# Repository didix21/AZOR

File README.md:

# AZOR

This repository contains all the AZOR 1.0 board KiCad files.  

## About Hardware 

AZOR 1.0 is based on [DUET 0.85](http://reprap.org/wiki/Duet#Drive_numbers) created by [dc42](https://github.com/dc42). I have done very important modifications as delete Ethernet and micro SD ports. Instead, I have added a USB 2.0 port to read USB Sticks. 

Moreover, the integrated steppers A4982 have been deleted and instead of that, I have placed HEADER PINS to connect drivers as A4988 or DRV8825. 

## About Software 

AZOR 1.0 use [Marlin4AZOR](https://github.com/didix21/Marlin4AZOR), it is a modified version of work  done by [Wurstnase](https://github.com/Wurstnase). In other words it is based on [Marlin4Due](https://github.com/Wurstnase/Marlin4Due).

## Main Features

- MCU: 32-bits, ATSAM3X8E-AU.
- Port Expansion
- Support for drivers: A4982 and DRV8825.
- Two FAN PWM ports.
- PTS-Panel Header Pin port.
- SD Header Pin Port.
- USB 2.0 port.

## License

Marlin is published under the [GPL license](LICENSE).

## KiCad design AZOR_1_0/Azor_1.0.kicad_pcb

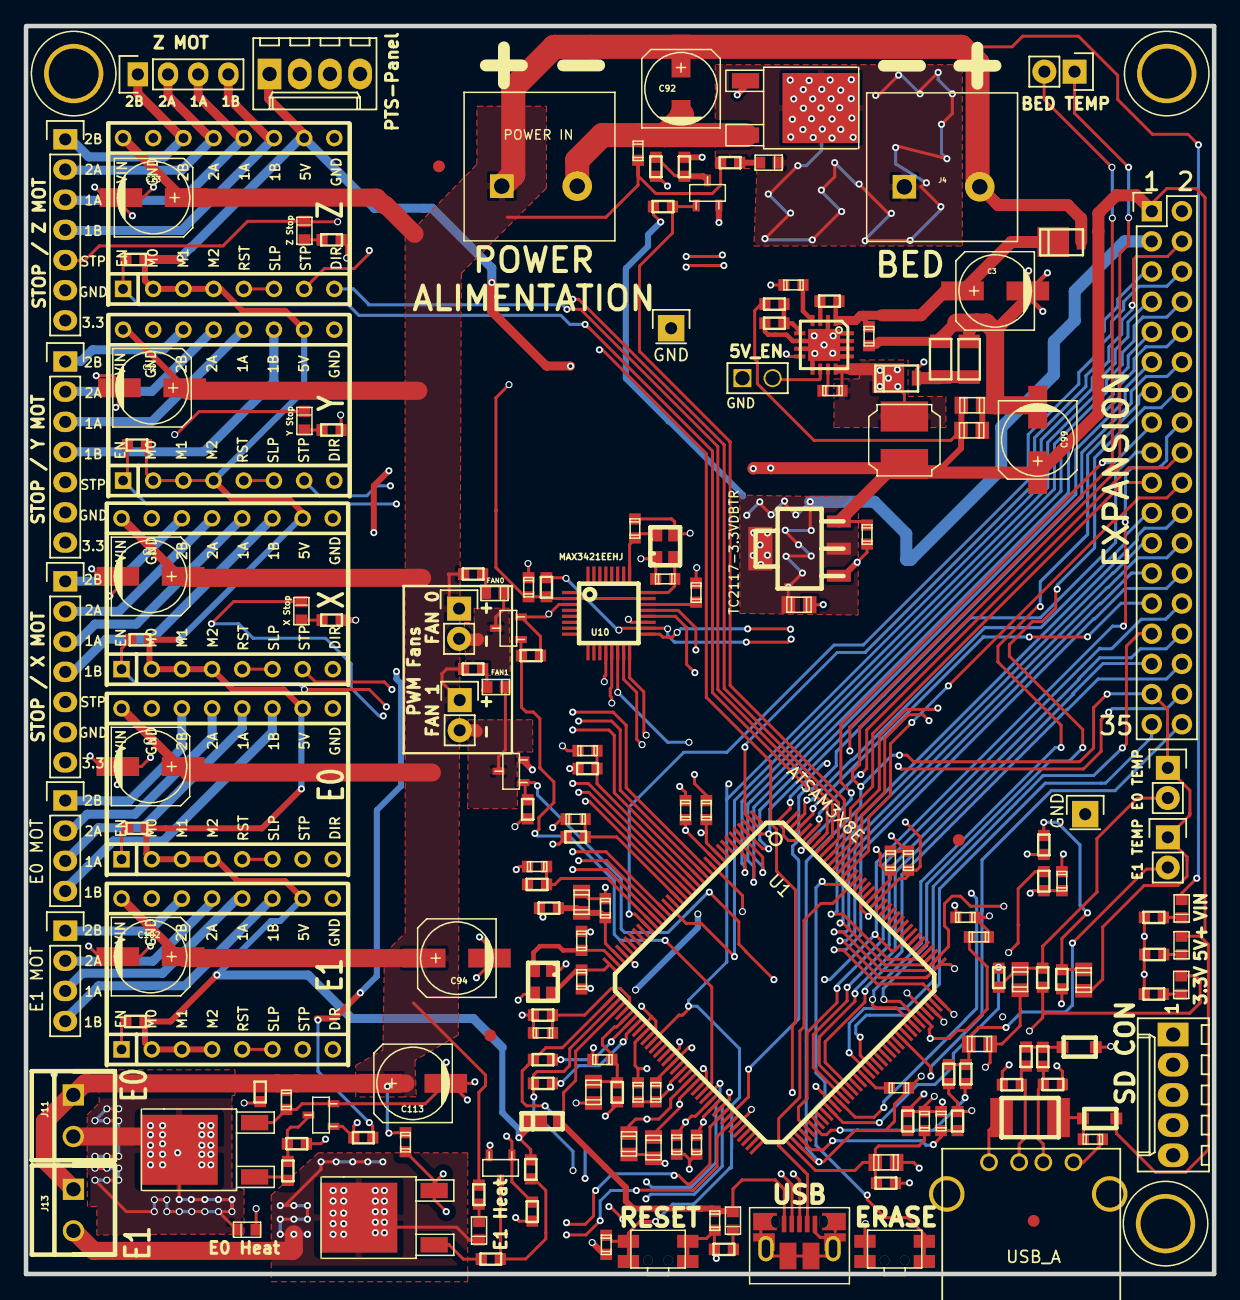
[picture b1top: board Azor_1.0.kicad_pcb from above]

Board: 4 copper layers, 100.0 x 105.0 mm, 180 parts (0 on the bottom side), 153 nets.

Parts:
C1: 2u2; C_0603
C2: 0u01; C_0603
C3, C22, C23, C32, C33, C92, C94, C99, C102, C113: 100u; C_ELEC_6.3x7.7
C4, C18, C19, C47, C53, C97, C98: 10u; C_0805
C5, C40, C41, C42, C43, C46, C48, C49, C50, C51, C52, C60, C62, C64, C67, C69, C70, C71, C72, C91, C93, C112: 0u1; C_0603
C13, C95: 1u; C_0603
C44, C45, C65: 10p; C_0603
C59, C61, C66, C68: 4u7; C_0805
C90: 10nF; C_0603
C96: 22nF; C_0603
C114, C117, C118: 100n; C_0603
C115, C116: 22p; C_0603
D1, D2: SS3P4; DO-220AA
D3: USB; D_0603
D6: Bed Heat; D_0603
D7: E0 Heat; D_0603
D8: FAN0; D_0603
D9: Y Stop; D_0603
D10: Z Stop; D_0603
D12: X Stop; D_0603
D13: SS14M; uSMA
D15: VIN; D_0603
D16: 3.3V; D_0603
D17: 5V+; D_0603
D20: E1 Heat; D_0603
D21: FAN1; D_0603
D50, D51: PGB1010604; R_0603
F1: L-EUL1812; L_1812
Fid: VAL**; Fiducial
Fid#2, Fid#3, Fid#4: VAL**; Fiducial
J1: CONN2X18; Pin_Header_Straight_2x18
J4: BED HEAT; TERM_2-WAY_6.35mm
J5: BED TEMP; Pin_Header_Straight_1x02
J6: E1 MOT; Pin_Header_Straight_1x04
J7: STOP / Z MOT; Pin_Header_Straight_1x07
J8: STOP / Y MOT; Pin_Header_Straight_1x07
J9: STOP / X MOT; Pin_Header_Straight_1x07
J10: E0 MOT; Pin_Header_Straight_1x04
J11: E0 HEAT; PHOENIX_CONNECTOR_2
J12: E0 TEMP; Pin_Header_Straight_1x02
J13: E1 HEAT; PHOENIX_CONNECTOR_2
J14: E1 TEMP; Pin_Header_Straight_1x02
J15: Z MOT; Pin_Header_Straight_1x04
J22: USB; uUSB_new
J23: POWER IN; TERM_2-WAY_6.35mm
J25: FAN 0; Pin_Header_Straight_1x02
J26, J27: GND; Pin_Header_Straight_1x01
J29: FAN 1; Pin_Header_Straight_1x02
J30: PanelDUE; Molex_KK-6410-04_04x2.54mm_Straight
J31: CONN_01X05; Molex_KK-6410-05_05x2.54mm_Straight
JP9: 5V_EN; JUMPER
L1: 10uH; L_6x6
L3, L4, L5, L6, L7: 100Mhz; R_0603
L20, L21: BLM21; L_0805
P1: USB_A
R1: 3K3; R_0603
R2, R3: 39R 1%; R_0603
R18, R22, R60, R79: 470R; R_0603
R19, R21, R53: 4K7; R_0603
R20, R23, R97: 220R; R_0603
R24, R80, R81, R82, R99, R103: 10K; R_0603
R25, R77, R78: 100k; R_0603
R26, R28, R38, R40, R89: 10k; R_0603
R48: 6k8; R_0603
R55, R65, R67, R68, R98, R100: 4k7; R_0603
R56, R57, R58, R59: 100R; R_0603
R61: 2K15; R_0603
R69, R70, R72: 680R; R_0603
R84: 100K; R_0603
R85, R86: 0R1; R_1206
R87: 3K92; R_0603
R88: 750R; R_0603
R101, R102: 22R 1%; R_0603
S1: RESET; SW_LITTLE_PCB_1
S2: ERASE; SW_LITTLE_PCB_1
TR1, TR3, TR6: BSH105; SOT-23
TR2, TR4, TR8: IPD036N04L; D-PAK
TR5, TR9: PMV40UN2; SOT-23
U1: ATSAM3X8E; LQFP144
U2: TC2117-3.3VDBTR; SOT-223
U3: A4403; QFN16-4x4
U5, U6, U7, U8, U11: DRV8825_; DRV8825
U10: MAX3421EEHJ
X2, X5: CRYSTAL_4PIN; CRYSTAL_KX_7_12MHz

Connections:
+3.3V: C2.1, C4.1, C46.1, C47.1, C48.1, C49.1, C50.1, C51.1, C118.2, D16.1, J1.3, J7.7, J8.7, J9.7, L3.2, L4.2, L5.2, R19.1, R21.1, R25.2, R53.1, R69.2, R70.2, R72.2, R77.2, R78.2, R103.2, S2.3, S2.4, U1.11, U1.52, U1.57, U1.62, U1.105, U1.125, U2.2, U2.4, U10.2, U10.23
+5V: C95.1, C97.1, C98.1, C99.1, D13.2, D17.1, J1.1, J30.1, L1.1, L21.1, R18.1, R22.1, R26.1, R28.1, R38.1, R40.1, R79.1, R87.2, R89.1, U2.3, U5.2, U5.3, U5.4, U5.10, U6.2, U6.3, U6.4, U6.10, U7.2, U7.3, U7.4, U7.10, U8.2, U8.3, U8.4, U8.10, U11.2, U11.3, U11.4, U11.10
/Processor/VDDCORE: C52.1, C68.1, C69.1, C70.1, C71.1, C72.1, L6.1, U1.10, U1.45, U1.56, U1.61, U1.104, U1.124
AD0: J1.30, U1.85
AD13: J1.29, U1.91
AD14: J1.35, U1.92
ADVREF: C64.1, L5.1, U1.75
BED-: D6.2, J4.1, TR2.D
BED_PWM: R77.1, TR1.G, U1.135
BED_THERMISTOR: C19.1, J5.2, R21.2, R81.1
D+: R102.1, U10.21
D-: R101.1, U10.20
DFSDM: R3.2, U1.43
DFSDP: R2.2, U1.42
DHSDM: J22.2, R3.1, U1.38
DHSDP: J22.3, R2.1, U1.37
E0-: D7.2, J11.2, TR4.D
E0_DIR: U1.24, U8.8
E0_EN: R40.2, U1.25, U8.1
E0_MOT_1A: J10.3, U8.12
E0_MOT_1B: J10.4, U8.11
E0_MOT_2A: J10.2, U8.13
E0_MOT_2B: J10.1, U8.14
E0_PWM: R78.1, TR3.G, U1.66
E0_STEP: U1.23, U8.7
E0_STOP: C43.1, R59.1, U1.26
E0_THERMISTOR: C18.1, J12.2, R19.2, R80.1
E1-: D20.2, J13.2, TR8.D
E1_DIR: U1.60, U11.8
E1_EN: R89.2, U1.63, U11.1
E1_MOT_1A: J6.3, U11.12
E1_MOT_1B: J6.4, U11.11
E1_MOT_2A: J6.2, U11.13
E1_MOT_2B: J6.1, U11.14
E1_PWM: R25.1, TR6.G, U1.64
E1_STEP: U1.67, U11.7
E1_THERMISTOR: C53.1, J14.2, R53.2, R82.1
FAN0-: D8.2, J25.2, TR5.D
FAN0_PWM: R24.1, TR5.G, U1.59
FAN1-: D21.2, J29.2, TR9.D
FAN1_PWM: J1.16, R99.1, TR9.G, U1.116
GND: C1.2, C3.2, C4.2, C5.2, C13.2, C22.2, C23.2, C32.2, C33.2, C40.2, C41.2, C42.2, C43.2, C44.2, C45.2, C46.2, C47.2, C48.2, C49.2, C50.2, C51.2, C52.2, C59.2, C60.2, C61.2, C62.2, C64.2, C65.2, C66.2, C67.2, C68.2, C69.2, C70.2, C71.2, C72.2, C91.2, C92.2, C93.2, C94.2, C95.2, C97.2, C98.2, C99.2, C102.2, C112.2, C113.2, C114.2, C115.2, C116.2, C117.1, C118.1, J1.2, J7.6, J8.6, J9.6, J22.5, J22.CE, J23.2, J26.1, J27.1, J30.2, JP9.1, L7.1, L20.1, P1.4, P1.5, R1.2, R24.2, R48.2, R55.2, R60.2, R61.2, R85.1, R86.1, R88.1, R99.2, S1.1, S1.2, TR1.S, TR2.S, TR3.S, TR4.S, TR5.S, TR6.S, TR8.S, TR9.S, U1.12, U1.33, U1.44, U1.46, U1.51, U1.54, U1.58, U1.106, U1.126, U2.1, U3.2, U3.6, U3.7, U3.9, U3.13, U3.14, U3.15, U3.16, U3.17, U5.9, U5.15, U6.9, U6.15, U7.9, U7.15, U8.9, U8.15, U10.3, U10.19, U11.9, U11.15, X2.2, X2.4, X5.2, X5.4
unnamed: C1.1, C3.1, D1.2, R84.1, U3.1
unnamed: C5.1, U3.4
unnamed: C44.1, U1.35, X2.3
unnamed: C45.1, U1.36, X2.1
unnamed: C65.1, R48.1, U1.40
unnamed: C66.1, C67.1, L6.2, U1.34
unnamed: C90.2, U1.90
unnamed: C96.1, U3.11
unnamed: C96.2, D2.2, L1.2, U3.12
unnamed: C114.1, F1.2, L21.2
unnamed: C115.1, U10.25, X5.1
unnamed: C116.1, U10.24, X5.3
unnamed: C117.2, U10.22
unnamed: D2.1, R85.2, R86.2, U3.8
unnamed: D3.2, R1.1
unnamed: D6.1, R65.1
unnamed: D7.1, R67.1
unnamed: D8.1, R68.1
unnamed: D9.1, R69.1
unnamed: D10.1, R70.1
unnamed: D12.1, R72.1
unnamed: D15.2, R55.1
unnamed: D16.2, R60.1
unnamed: D17.2, R61.1
unnamed: D20.1, R98.1
unnamed: D21.1, R100.1
unnamed: D50.1, D51.1, L20.2
unnamed: D50.2, P1.2, R101.2
unnamed: D51.2, P1.3, R102.2
unnamed: F1.1, P1.1
unnamed: JP9.2, U3.10
unnamed: R18.2, R20.1, TR1.D
unnamed: R20.2, TR2.G
unnamed: R22.2, R23.1, TR3.D
unnamed: R23.2, TR4.G
unnamed: R79.2, R97.1, TR6.D
unnamed: R80.2, U1.82
unnamed: R81.2, U1.83
unnamed: R82.2, U1.78
unnamed: R84.2, U3.3
unnamed: R87.1, R88.2, U3.5
unnamed: R97.2, TR8.G
unnamed: S2.1, S2.2, U1.130
unnamed: U5.5, U5.6
unnamed: U6.5, U6.6
unnamed: U7.5, U7.6
unnamed: U8.5, U8.6
unnamed: U11.5, U11.6
PA14: J1.8, U1.7
PB14/PWMH2: J1.18, U1.140
PB16/DAC1: J1.28, U1.77
PB22: J1.34, U1.141
PB23: J1.27, U1.142
PB24: J1.21, U1.143
PC7_PWMH2: J1.17, U1.65
PC17: J1.36, U1.99
PC20_PWMH4: J1.20, U1.131
PC21_INT_D9: R103.1, U1.132, U10.18
PC22_GPX_D8: U1.133, U10.17
PC23_PWML6: J1.19, U1.134
PC28: J1.15, U1.139
PC29: J1.13, J31.1, U1.102
PC30: J1.14, U1.103
PD9: J1.7, U1.22
RESET: C2.2, J1.4, J31.5, S1.3, S1.4, U1.47, U10.12
RXD0: J1.12, U1.3
RXD1: J1.10, U1.5
SPI0_MISO: J1.26, J31.4, U1.108, U10.15
SPI0_MOSI: J1.25, J31.2, U1.109, U10.16
SPI0_NPCS0: J1.23, U1.111, U10.14
SPI0_NPCS1: J1.22, U1.112
SPI0_SPCK: J1.24, J31.3, U1.110, U10.13
TWCK1: J1.32, U1.87
TWD1: J1.31, U1.86
TXD0: J1.11, U1.4
TXD1: J1.9, U1.6
UOTGID: J22.4, U1.129
URXD: J1.5, J30.3, U1.27
UTXD: J1.6, J30.4, U1.2
VBUS: C13.1, D3.1, D13.1, J22.1, U1.39
VDDANA: C61.1, C62.1, L4.1, U1.73
VDDUTMI: C59.1, C60.1, L3.1, U1.41
VSSA: C18.2, C19.2, C53.2, C90.1, J1.33, J5.1, J12.1, J14.1, L7.2, U1.74
V_IN: C22.1, C23.1, C32.1, C33.1, C91.1, C92.1, C93.1, C94.1, C102.1, C112.1, C113.1, D1.1, D15.1, J4.2, J11.1, J13.1, J23.1, J25.1, J29.1, R65.2, R67.2, R68.2, R98.2, R100.2, U5.16, U6.16, U7.16, U8.16, U11.16
X_DIR: U1.18, U5.8
X_EN: R26.2, U1.19, U5.1
X_MOT_1A: J9.3, U5.12
X_MOT_1B: J9.4, U5.11
X_MOT_2A: J9.2, U5.13
X_MOT_2B: J9.1, U5.14
X_STEP: U1.17, U5.7
X_STOP: C40.1, R56.1, U1.20
X_STOP_CONN: D12.2, J9.5, R56.2
Y_DIR: U1.14, U7.8
Y_EN: R38.2, U1.15, U7.1
Y_MOT_1A: J8.3, U7.12
Y_MOT_1B: J8.4, U7.11
Y_MOT_2A: J8.2, U7.13
Y_MOT_2B: J8.1, U7.14
Y_STEP: U1.13, U7.7
Y_STOP: C41.1, R57.1, U1.16
Y_STOP_CONN: D9.2, J8.5, R57.2
Z_DIR: U1.137, U6.8
Z_EN: R28.2, U1.138, U6.1
Z_MOT_1A: J7.3, J15.3, U6.12
Z_MOT_1B: J7.4, J15.4, U6.11
Z_MOT_2A: J7.2, J15.2, U6.13
Z_MOT_2B: J7.1, J15.1, U6.14
Z_STEP: U1.136, U6.7
Z_STOP: C42.1, R58.1, U1.84
Z_STOP_CONN: D10.2, J7.5, R58.2

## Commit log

2016-09-08 Modified Readme.md
2016-09-08 Modified Read.md
2016-09-08 Readme.md logo
2016-09-08 Readme.md logo little
